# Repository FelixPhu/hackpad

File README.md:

# padpadpadpadpadpad

Padpadpadpadpadpad (or pad^6) is a simple hackpad with 6 keys and 2 WS2812B LEDs. Made for fun + learning experience

## Features
- 6 mechanical keys
- 2 WS2812B LEDs
- A 3D printed case made of 3 parts
- QMK Firmware

## CAD
The case is made of 3 parts (e.g. top plate, middle, bottom).

Made in Onshape

## PCB
The PCB was designed in KiCad. 

I found the silkscreen on the internet.

Schematic:

## Firmware
This hackpad uses QMK Software for everything.
[https://qmk.fm/](url)

## BOM

Here's everything you need to make this hackpad:
- 1 XIAO RP2040
- 6 Cherry MX Switches
- 6 DSA Keycaps
- 2 SK6812 MINI-E LEDS
- 1 Case (3 3D printed parts)
- Custom PCB
- 4 M3x16mm screws
- 4 M3x5mx4mm heatset insert

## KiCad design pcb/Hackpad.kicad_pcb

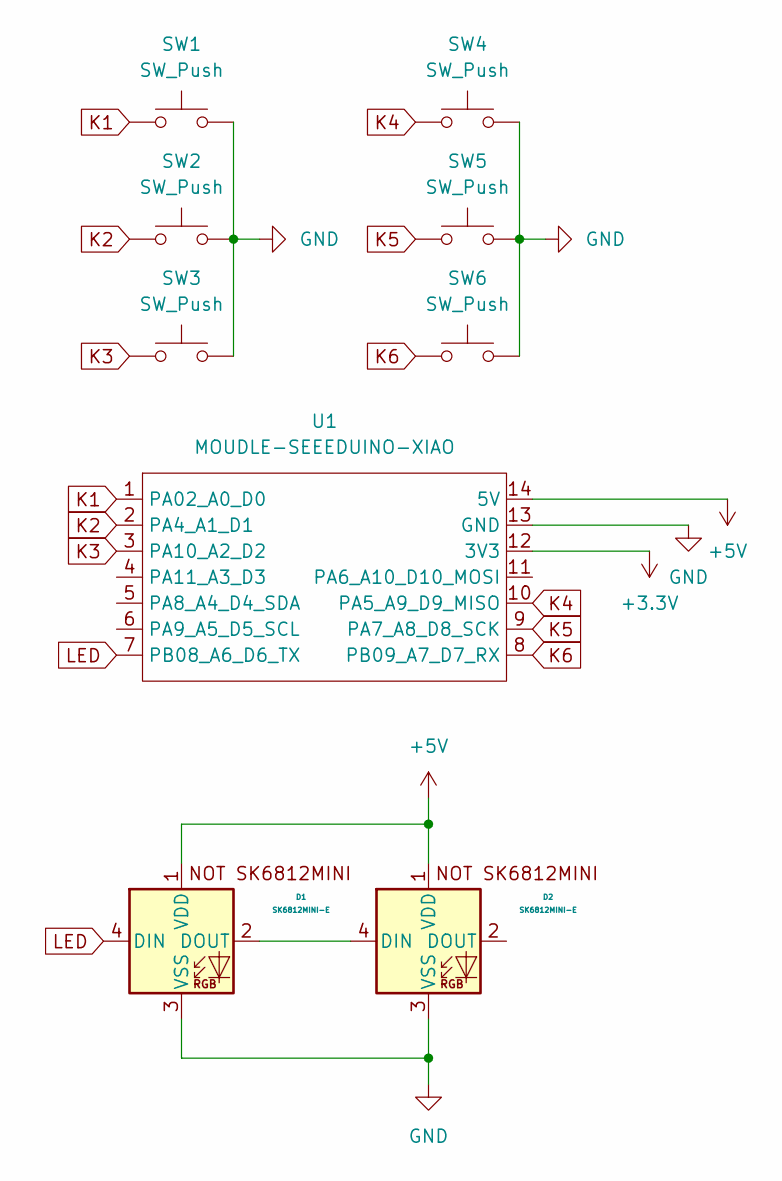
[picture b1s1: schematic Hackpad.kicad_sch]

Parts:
D1, D2: SK6812MINI-E; SK6812MINI-E_fixed
SW1, SW2, SW3, SW4, SW5, SW6: SW_Push; SW_Cherry_MX_1.00u_PCB
U1: MOUDLE-SEEEDUINO-XIAO; XIAO-Generic-Hybrid-14P-2.54-21X17.8MM

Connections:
+3.3V: U1.12 (3V3)
+5V: D1.1 (VDD), D2.1 (VDD), U1.14 (5V)
GND: D1.3 (VSS), D2.3 (VSS), SW1.2, SW2.2, SW3.2, SW4.2, SW5.2, SW6.2, U1.13 (GND)
K1: SW1.1, U1.1 (PA02_A0_D0)
K2: SW2.1, U1.2 (PA4_A1_D1)
K3: SW3.1, U1.3 (PA10_A2_D2)
K4: SW4.1, U1.10 (PA5_A9_D9_MISO)
K5: SW5.1, U1.9 (PA7_A8_D8_SCK)
K6: SW6.1, U1.8 (PB09_A7_D7_RX)
LED: D1.4 (DIN), U1.7 (PB08_A6_D6_TX)
unnamed: D1.2 (DOUT), D2.4 (DIN)

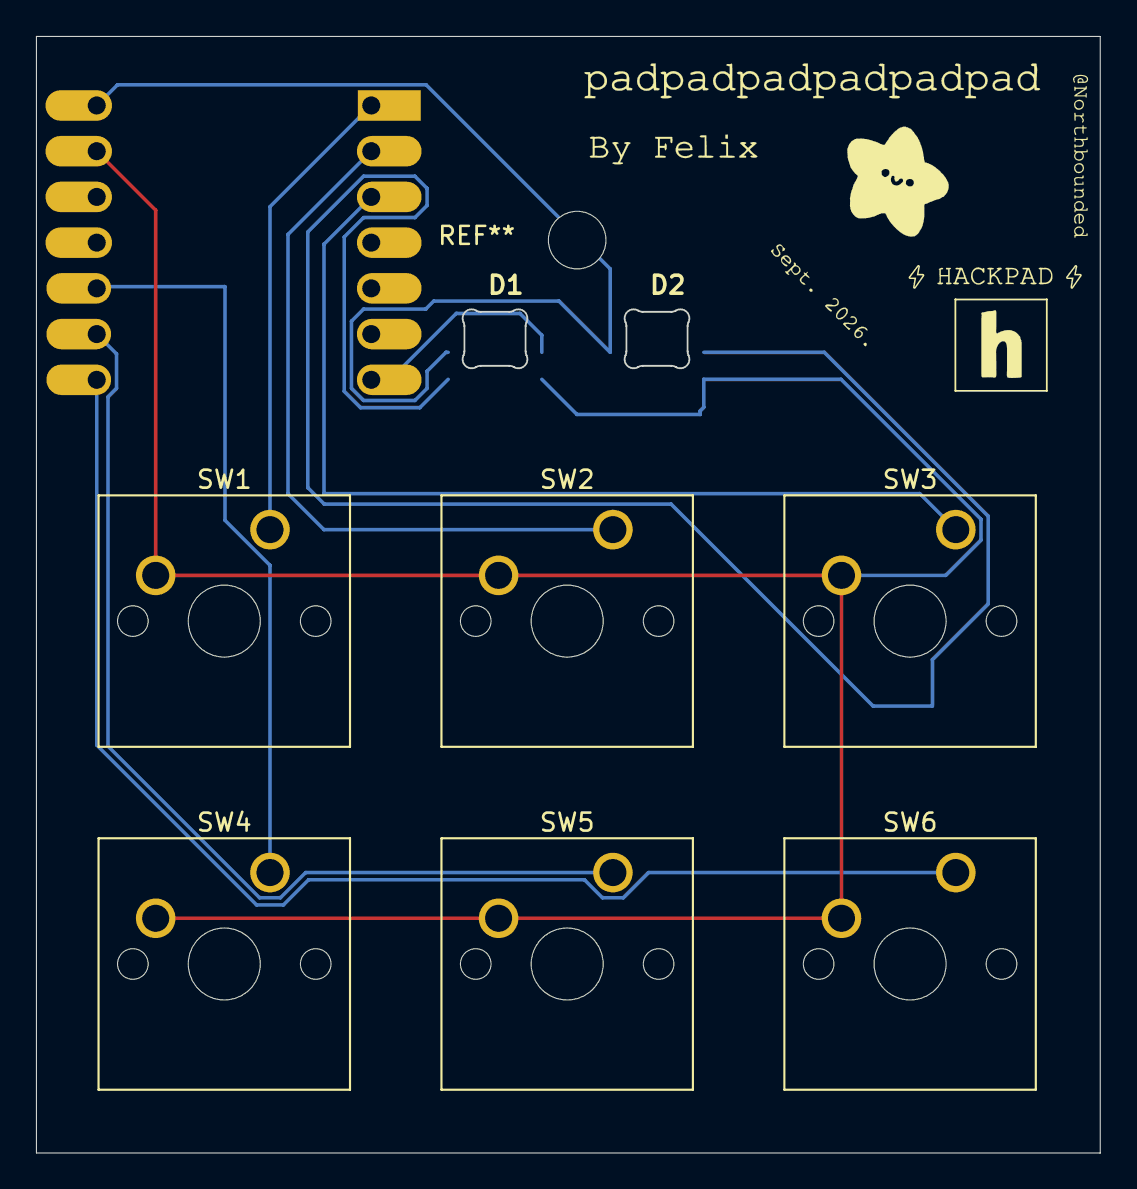
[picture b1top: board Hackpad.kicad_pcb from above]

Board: 2 copper layers, 59.1 x 62.0 mm, 9 parts (1 on the bottom side), 10 nets.
